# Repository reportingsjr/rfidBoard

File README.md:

General
=========
This repository has the source for a PCB that uses Power over Ethernet (PoE) to power an STM32F103 microcontroller. It has a 10mbit ethernet MAC/PHY and  3.3V (.6A, 2W) and 12V (.5A, 6W) supplies fed from a 5V (1.8A, 9W) power rail. This gives this board the capability to provide power and control for quite a few different peripherals. The first use of the circuit boards and software in this repository is to provide a lower cost and more versatile RFID based entry method for a local hackerspace, Hive13.

In this repository you will currently find two main sections: hardware, and software. The hardware section contains the KiCad files for the PoE (power over ethernet)/micro board and the rfid transceiver board (rfidBoad). The software section contains the software/firmware for the stm32f103 to support the wanted functionality (currently ethernet comms and rfid/access control).
RFID/NFC board with ethernet+PoE with numerous I/Os.

Hardware
=========

The hardware consists of two separate boards: rfidBoard and PoE. rfidBoard is simply an rfid transceiver and antenna. PoE has an STM32F103 microcontroller which is connected to a 10mbit ethernet MAC/PHY. It alsohas a power over ethernet supply that provides 5V@1.8A total. This 5 volt supply provides power for a 3.3V supply and a 12V supply. The 3.3V supply is meant for powering ICs and other electronics while the 12V supply is meant for providing power to electronic door latches (solenoids).

rfid antenna
ST Micro's antenna.exe (can be found with google) was used to calculate the antenna size for an approximately 430nH antenna. A similar antenna of different shapes can be created by using the equations in the paper "Simple Accurate Expressions for Planar Spiral Inductances" (DOI 10.1109/4.792620). The parameters I used in antenna.exe are as follows: 2 turns, 8 segments, 1mm wide conductor, 0.25mm spacing between conductors, 35um conductor thickness, and 40mm by 40mm width and length.

Software
========
There is no software or firmware set up or written yet!
It will consist of a TCP/IP stack, an RFID stack, and a user access stack.

programs needed for compilation on fedora:
sudo yum install arm-none-eabi-gcc-cs arm-none-eabi-newlib scons

To program the board an STLINK v2 programmer is needed as well as stlink (on linux).

When cloning from git cd in to software/libopencm3 and run:
`git submodule init`
`git submodule update`

To flash the board with gdb and an st-link device:
In a separate terminal run the st-link server `st-util -1`
In another terminal run `arm-none-eabi-gdb firmware.elf`
Then in gdb run `tar ext :4242`, `load`, and finally either `continue` or `run`.

Datasheets
========
The datasheets directory contains some datasheets for different chips on board.
Currently it only contains STM32 microcontroller stuff.
They are large and don't fit well in to a git repository, but it helps keep
everything together and makes things easier to investigate down the line.

Notes and Issues
=========
* TODO: Add fuses on to POE board to protect circuitry.
* Several of the components in the PoE circuitry get WAY too hot.
* C5 (4.7uF cap on the PoE input) should have the negative pin connected to  GNDA/Pout rather than VPortN.
* ~~The 12V power supply current rating pretty much maxes out what the PoE can theoretically supply. Probably should derate the 12V supply quite a lot. This means that the 3.3V, 5V, and 12V will interfere with each other which is bad.~~ Updated current rating to 500mA which provides an ok margin for total power.
* ~~D1 may need to be unidirectional. The part specified in the BOM is currently bidirectional.~~ D1 should be a schottky!
* D2 is actually a zener, not a schottky as currently shown.
* *The footprint for U1 (LTC4267) is undersized.*

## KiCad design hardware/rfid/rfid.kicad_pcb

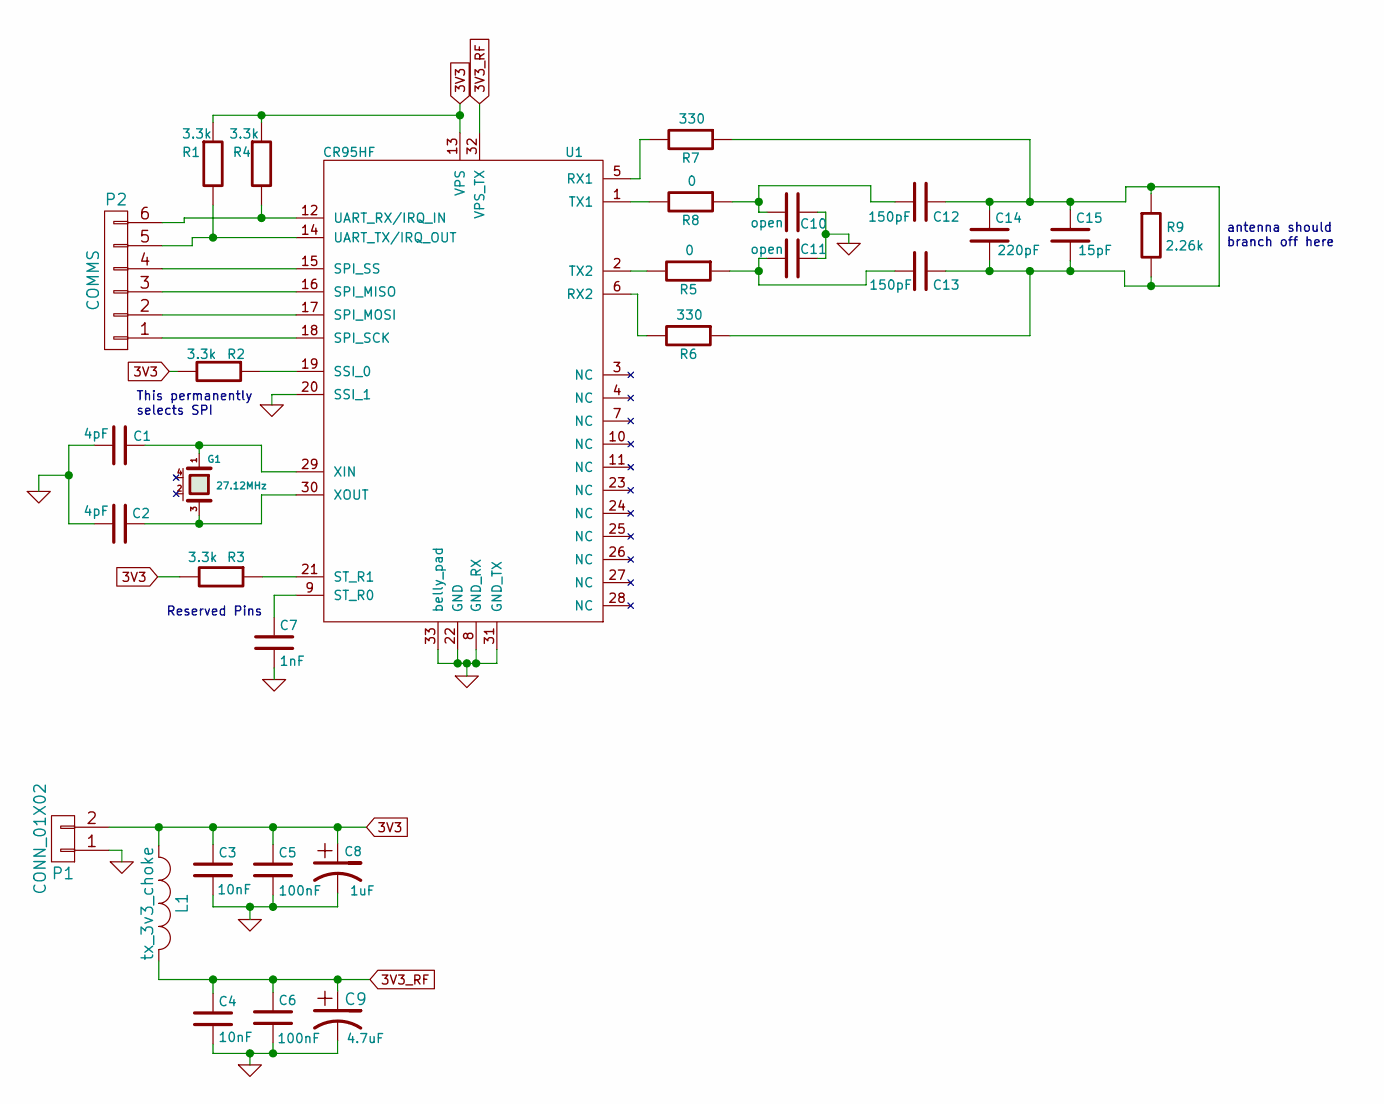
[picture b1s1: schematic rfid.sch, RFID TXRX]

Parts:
C1, C2: 4pF; SMD-0603
C3, C4: 10nF; SMD-0603
C5, C6: 100nF; SMD-0603
C7: 1nF; SMD-0603
C8: 1uF; SMD-0603
C9: 4.7uF; SMD-0805
C10, C11: open; SMD-0603
C12, C13: 150pF; SMD-0603
C14: 220pF; SMD-0603
C15: 15pF; SMD-0603
G1: 27.12MHz; 2x1.6_crystal
L1: tx_3v3_choke; SMD-0603
P1: CONN_01X02; JST_PH_2pin_side
P2: COMMS; JST_PH_6pin
R1, R2, R3, R4: 3.3k; SMD-0603
R5, R8: 0; SMD-0603
R6, R7: 330; SMD-0603
R9: 2.26k; SMD-0603
U1: CR95HF; QFN-32-1EP

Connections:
3V3: C3.1, C5.1, C8.1, L1.1, P1.2, R1.1, R2.2, R3.2, R4.1, U1.13 (VPS)
3V3_RF: C4.1, C6.1, C9.1, L1.2, U1.32 (VPS_TX)
GND: C1.2, C2.2, C3.2, C4.2, C5.2, C6.2, C7.2, C8.2, C9.2, C10.1, C11.1, P1.1, U1.8 (GND_RX), U1.20 (SSI_1), U1.22 (GND), U1.31 (GND_TX), U1.33 (belly_pad)
unnamed: C1.1, G1.1, U1.29 (XIN)
unnamed: C2.1, G1.3, U1.30 (XOUT)
unnamed: C7.1, U1.9 (ST_R0)
unnamed: C10.2, C12.2, R8.1
unnamed: C11.2, C13.2, R5.1
unnamed: C12.1, C13.1, C14.1, C14.2, C15.1, C15.2, R6.1, R7.1, R9.1, R9.2
unnamed: P2.1, U1.18 (SPI_SCK)
unnamed: P2.2, U1.17 (SPI_MOSI)
unnamed: P2.3, U1.16 (SPI_MISO)
unnamed: P2.4, U1.15 (SPI_SS)
unnamed: P2.5, R1.2, U1.14 (UART_TX/IRQ_OUT)
unnamed: P2.6, R4.2, U1.12 (UART_RX/IRQ_IN)
unnamed: R2.1, U1.19 (SSI_0)
unnamed: R3.1, U1.21 (ST_R1)
unnamed: R5.2, U1.2 (TX2)
unnamed: R6.2, U1.6 (RX2)
unnamed: R7.2, U1.5 (RX1)
unnamed: R8.2, U1.1 (TX1)

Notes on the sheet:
Reserved Pins
This permanently selects SPI
antenna should branch off here

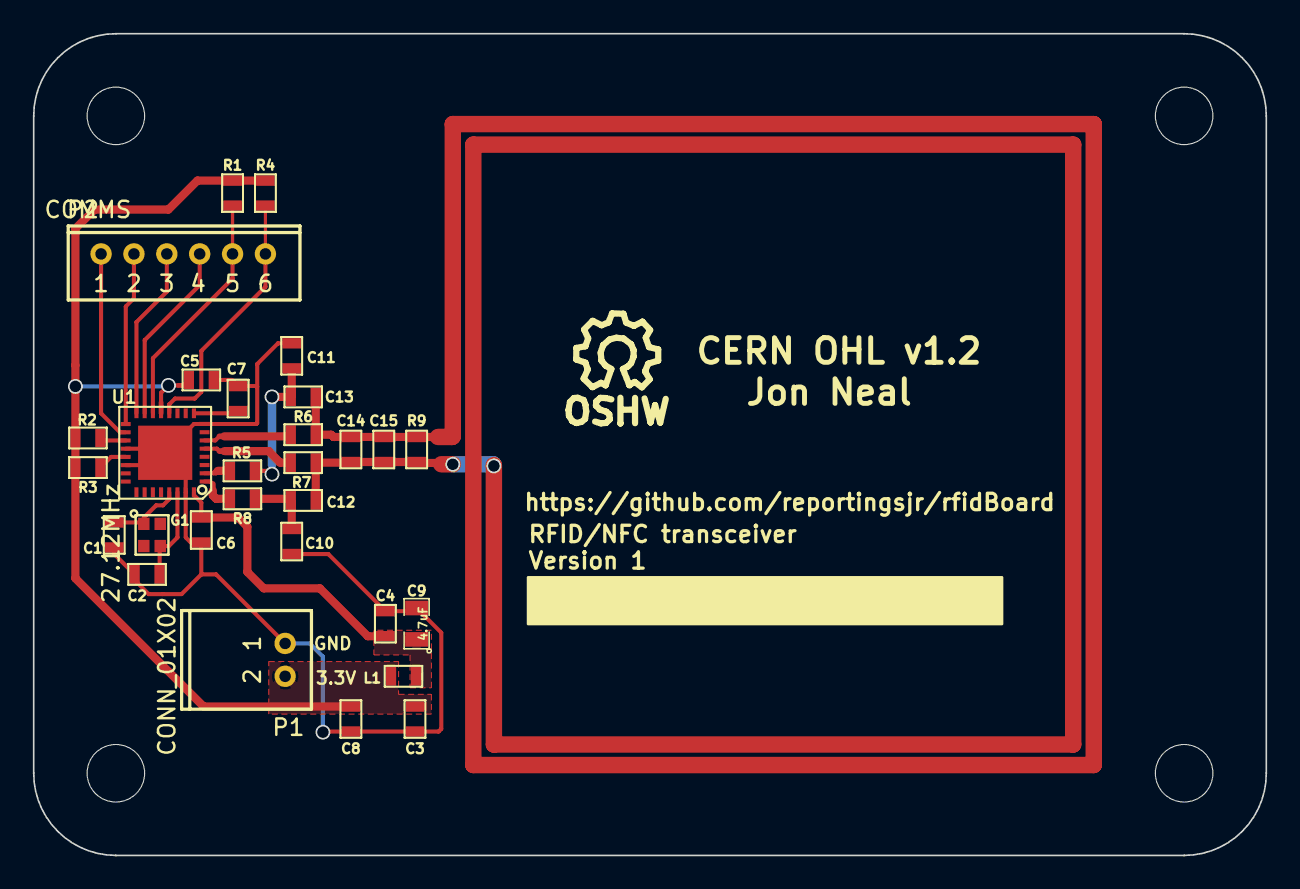
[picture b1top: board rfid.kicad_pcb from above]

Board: 2 copper layers, 75.0 x 50.0 mm, 34 parts (0 on the bottom side), 21 nets.

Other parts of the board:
MH: MountingHole_3-5mm_RevA_Date21Jun2010; MountingHole_3-5mm
MH#2, MH#3, MH#4: MountingHole_3-5mm_RevA_Date21Jun2010; MountingHole_3-5mm
SYM: Symbol_OSHW-Logo_SilkScreen_07Jul2012; Symbol_OSHW-Logo_SilkScreen

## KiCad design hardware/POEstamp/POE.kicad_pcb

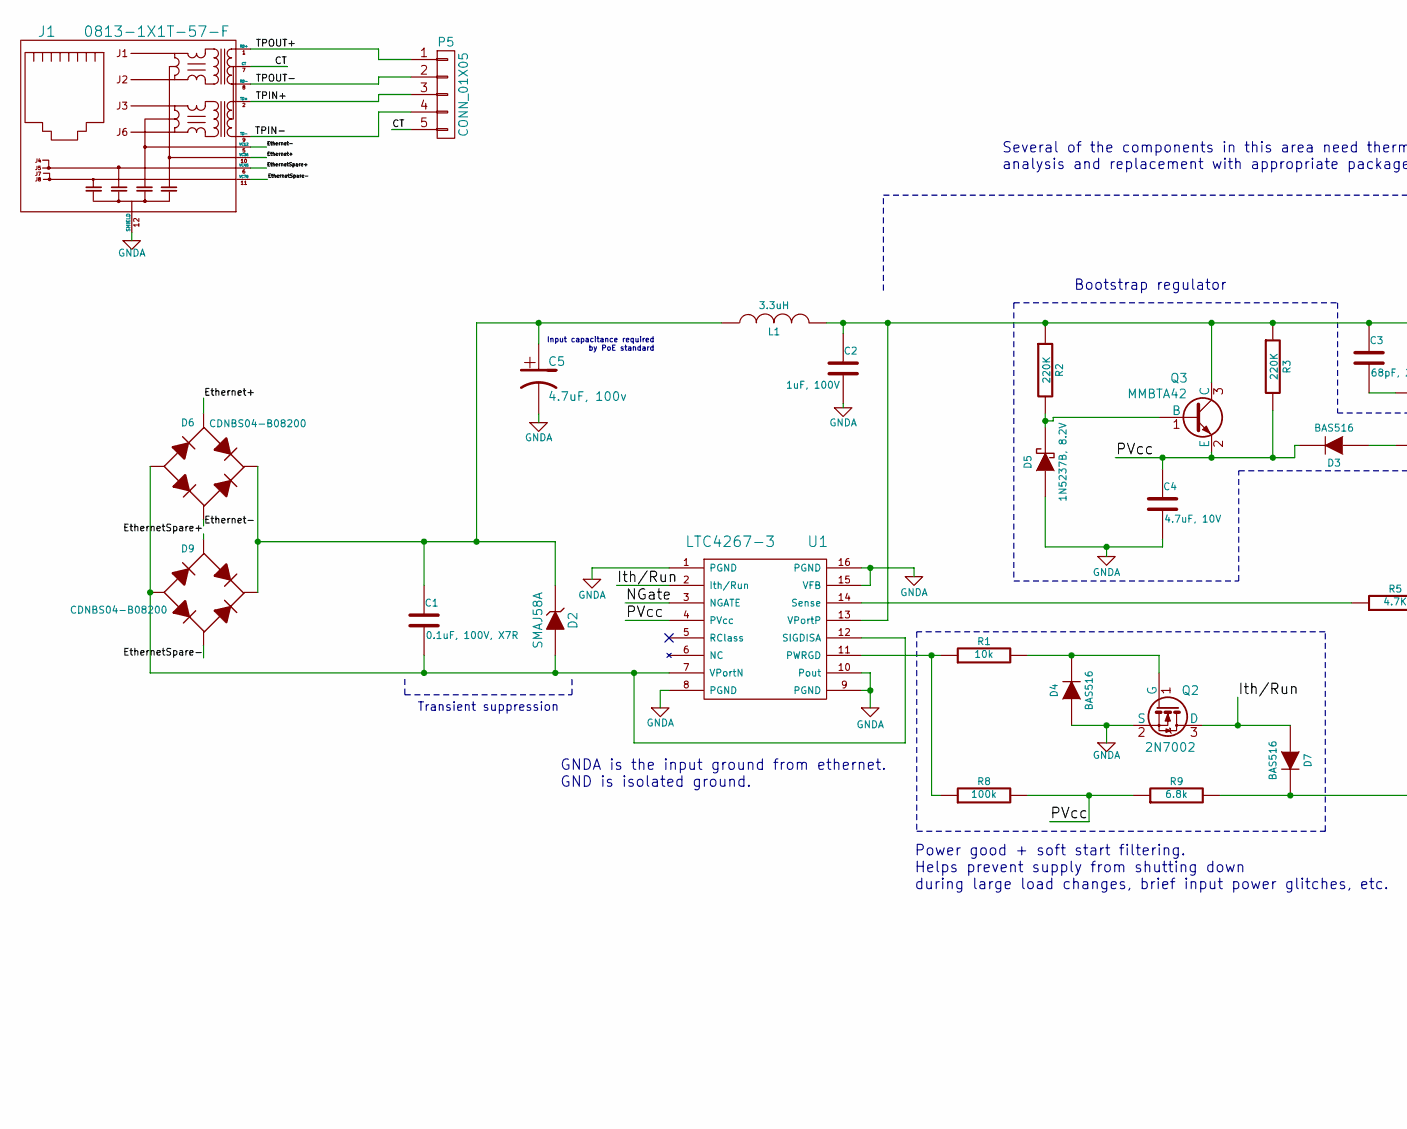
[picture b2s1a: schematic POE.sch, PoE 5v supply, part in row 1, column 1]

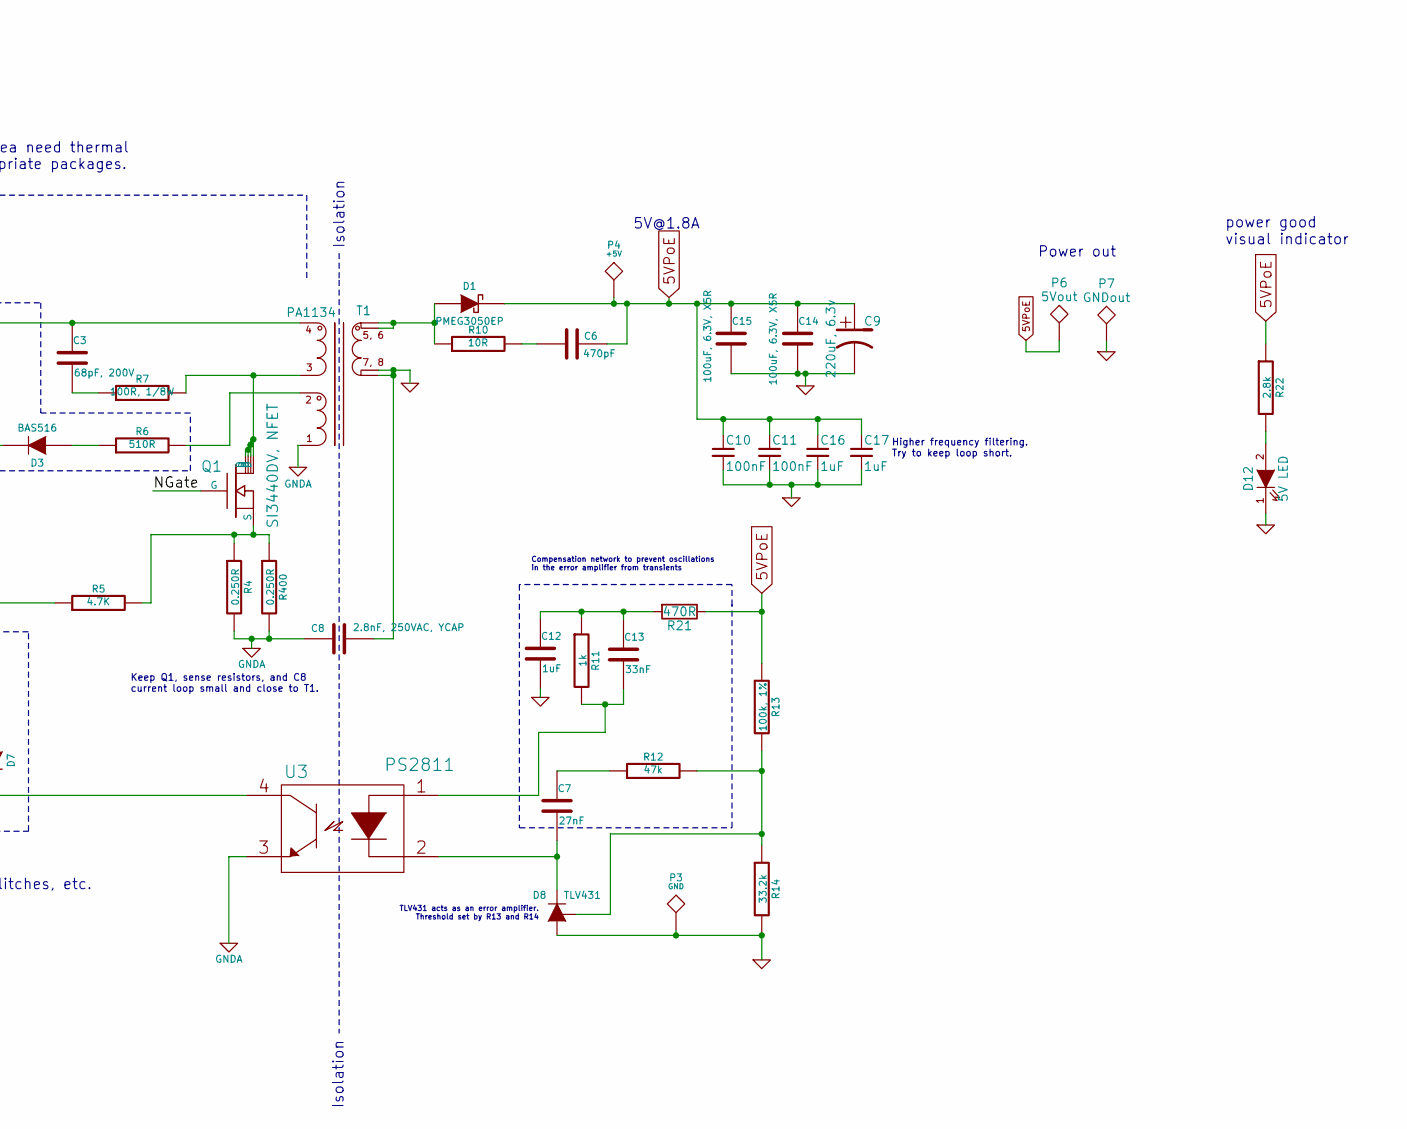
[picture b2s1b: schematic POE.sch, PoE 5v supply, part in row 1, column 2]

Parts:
C1: 0.1uF, 100V, X7R; CAPC2012X95
C2: 1uF, 100V; CAPC3216X180
C3: 68pF, 200V; CAPC1608X87
C4: 4.7uF, 10V; CAPC2012X135
C5: 4.7uF, 100v; EEE-2AA4R7UP
C6: 470pF; CAPC1608X90
C7: 27nF; CAPC2012X88
C8: 2.8nF, 250VAC, YCAP; CAPC4532X150
C9: 220uF, 6.3v; EEE-FK0J221P
C10, C11: 100nF; CAPC1608X90
C12, C16, C17: 1uF; CAPC1608X90
C13: 33nF; CAPC1608X95
C14, C15: 100uF, 6.3V, X5R; CAPC3216X180
D1: PMEG3050EP; SOD-128
D2: SMAJ58A; DIOM5436X265
D3, D4, D7: BAS516; SOD-523
D5: 1N5237B, 8.2V; SOD-123
D6, D9: CDNBS04-B08200; CDNBS04
D8: TLV431; SOT-23
D12: 5V LED; LED-0603
J1: 0813-1X1T-57-F
L1: 3.3uH; INDC2012X130
P3: GND; Measurement_Point_Round-SMD-Pad_Big
P4: +5V; Measurement_Point_Round-SMD-Pad_Big
P5: CONN_01X05; CONN-2MM-F-1x5
P6: 5Vout; 1pin
P7: GNDout; 1pin
Q1: SI3440DV, NFET; TSOP-6
Q2: 2N7002; SOT-23
Q3: MMBTA42; SOT-23
R1: 10k; RESC1608X55
R2, R3: 220K; RESC1608X55
R4, R400: 0.250R; RESC2013X65
R5: 4.7K; RESC1608X55
R6: 510R; RESC1608X55
R7: 100R, 1/8W; RESC2012X70
R8: 100k; RESC1608X55
R9: 6.8k; RESC1608X55
R10: 10R; RESC1608X55
R11: 1k; RESC1608X55
R12: 47k; RESC1608X55
R13: 100k, 1%; RESC1608X55
R14: 33.2k; RESC1608X55
R21: 470R; RESC1608X55
R22: 2.8k; RESC1608X55
T1: PA1134
U1: LTC4267-3; SOP63P600X175-16
U3: PS2811; SSOP-4

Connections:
5VPoE: C6.1, C9.1, C10.1, C11.1, C14.1, C15.1, C16.1, C17.1, D1.2 (K), P4.1, P6.1, R13.1, R21.1, R22.1
/CT: J1.7 (CT), P5.5
/Ethernet+: D6.3, J1.10 (VC36)
/Ethernet-: D6.2, J1.5 (VC12)
/EthernetSpare+: D9.3, J1.6 (VC45)
/EthernetSpare-: D9.2, J1.11 (VC78)
/Ith/Run: D7.1 (A), Q2.3 (D), U1.2 (Ith/Run)
/NGate: Q1.3 (G), U1.3 (NGATE)
/PVcc: C4.1, D3.2 (K), Q3.2 (E), R3.2, R8.2, R9.1, U1.4 (PVcc)
/TPIN+: J1.2 (TD+), P5.3
/TPIN-: J1.9 (TD-), P5.4
/TPOUT+: J1.1 (RD+), P5.1
/TPOUT-: J1.8 (RD-), P5.2
GND: C8.1, C9.2, C10.2, C11.2, C12.2, C14.2, C15.2, C16.2, C17.2, D8.3 (A), D12.1 (K), P3.1, P7.1, R14.2, T1.7, T1.8
GNDA: C2.2, C4.2, C5.2, C8.2, D4.1 (A), D5.1 (A), J1.12 (SHIELD), Q2.2 (S), R4.2, R400.2, T1.1, U1.1 (PGND), U1.8 (PGND), U1.9 (PGND), U1.10 (Pout), U1.15 (VFB), U1.16 (PGND), U3.3
unnamed: C1.1, C5.1, D2.1 (K), D6.1 (+), D9.1 (+), L1.1
unnamed: C1.2, D2.2 (A), D6.4 (-), D9.4 (-), U1.7 (VPortN), U1.12 (SIGDISA)
unnamed: C2.1, C3.1, L1.2, Q3.3 (C), R2.1, R3.1, T1.4, U1.13 (VPortP)
unnamed: C3.2, R7.1
unnamed: C6.2, R10.2
unnamed: C7.1, R12.1
unnamed: C7.2, D8.2 (K), U3.2
unnamed: C12.1, C13.1, R11.1, R21.2
unnamed: C13.2, R11.2, U3.1
unnamed: D1.1 (A), R10.1, T1.5, T1.6
unnamed: D3.1 (A), R6.1
unnamed: D4.2 (K), Q2.1 (G), R1.2
unnamed: D5.2 (K), Q3.1 (B), R2.2
unnamed: D7.2 (K), R9.2, U3.4
unnamed: D8.1 (ref), R12.2, R13.2, R14.1
unnamed: D12.2 (A), R22.2
unnamed: Q1.1 (D), Q1.2 (D), Q1.5 (D), Q1.6 (D), R7.2, T1.3
unnamed: Q1.4 (S), R4.1, R5.2, R400.1
unnamed: R1.1, R8.1, U1.11 (PWRGD)
unnamed: R5.1, U1.14 (Sense)
unnamed: R6.2, T1.2

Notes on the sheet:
GNDA is the input ground from ethernet. GND is isolated ground.
5V@1.8A
power good visual indicator
Keep Q1, sense resistors, and C8 current loop small and close to T1.
Power good + soft start filtering. Helps prevent supply from shutting down during large load changes, brief input power glitches, etc.
Isolation
Transient suppression
Input capacitance required by PoE standard
TLV431 acts as an error amplifier. Threshold set by R13 and R14
Compensation network to prevent oscillations in the error amplifier from transients
Bootstrap regulator
Higher frequency filtering. Try to keep loop short.
Power out
Several of the components in this area need thermal analysis and replacement with appropriate packages.

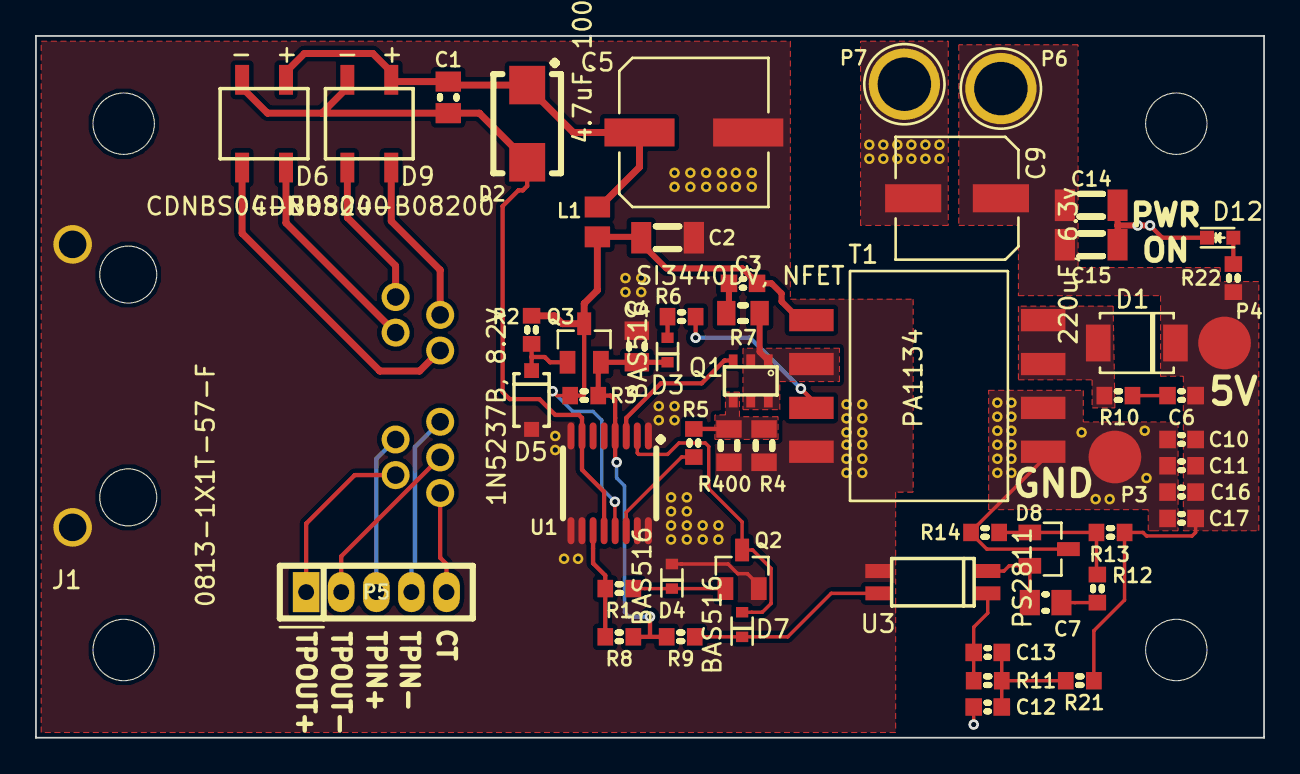
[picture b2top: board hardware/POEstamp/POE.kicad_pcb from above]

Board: 2 copper layers, 70.0 x 40.0 mm, 57 parts (1 on the bottom side), 36 nets.

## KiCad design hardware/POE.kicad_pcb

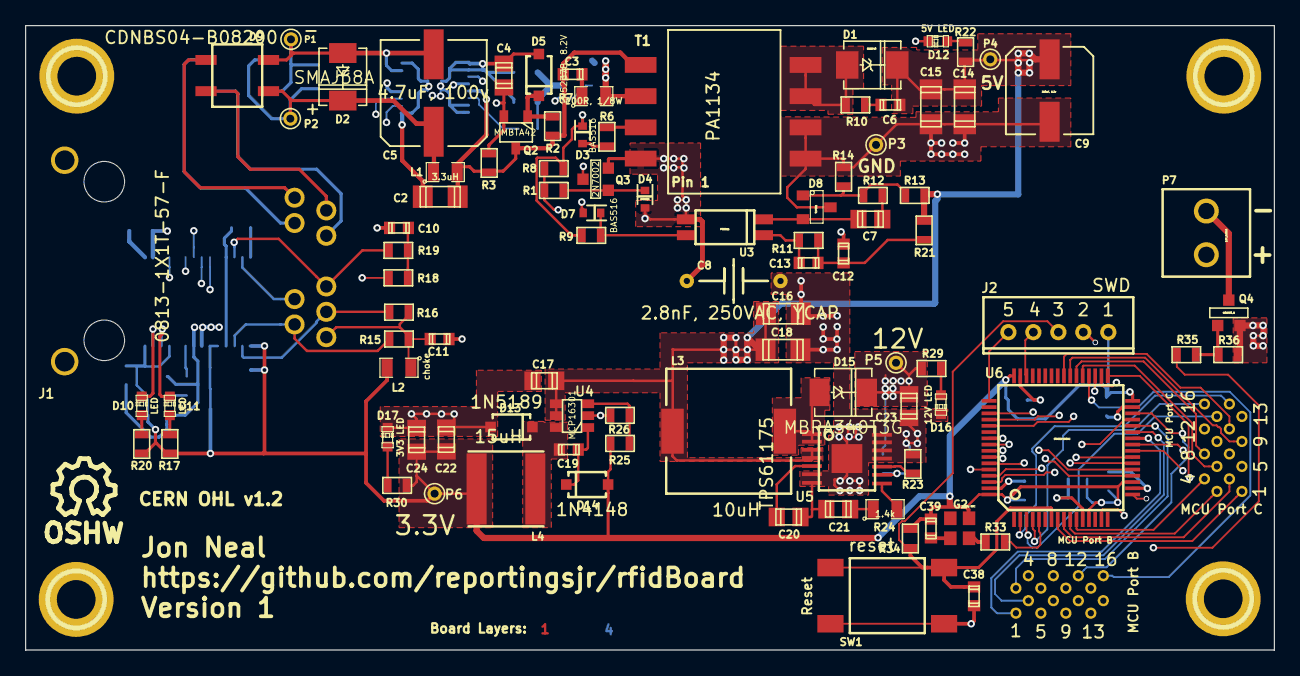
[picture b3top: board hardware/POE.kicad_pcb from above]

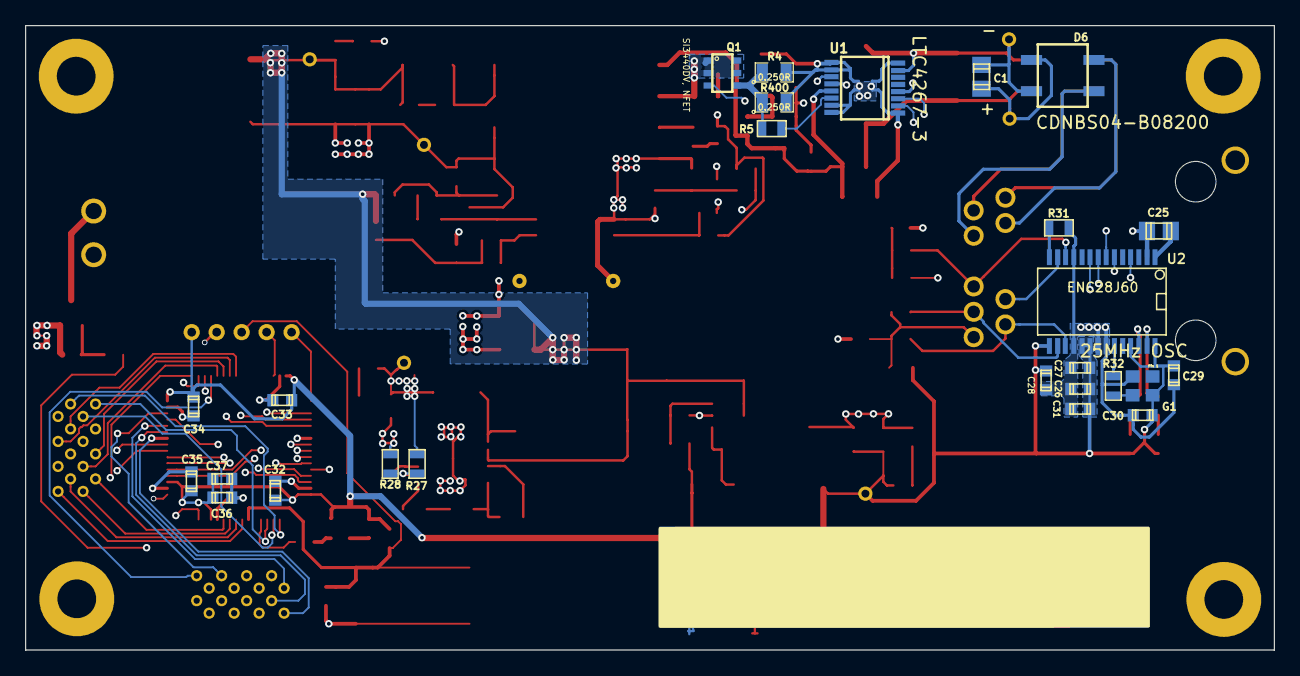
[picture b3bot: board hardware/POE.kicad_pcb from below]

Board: 4 copper layers, 100.0 x 50.0 mm, 127 parts (26 on the bottom side), 104 nets.

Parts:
1PIN, 1PIN#2, 1PIN#3, 1PIN#4: P***; 1pin
C1: 0.1uF, 100V, X7R; c_0805
C2: 1uF, 100V; c_1206
C3: 68pF, 200V; c_0603
C4: 4.7uF, 10V; c_0805
C5: 4.7uF, 100v; EEE-2AA4R7UP
C6: 470pF; c_0603
C7: 27nF; c_0805
C8: 2.8nF, 250VAC, YCAP; kemet_C900
C9: 220uF, 6.3v; EEE-FK0J221P
C10, C11: 10nF; c_0603
C12, C31, C37: 1uF; c_0603
C13: 33nF; c_0603
C14, C15: 100uF, 6.3V, X5R; c_1206
C16, C18: 10uF; c_1206
C17, C22, C24, C25: 10uF; c_0805
C19, C26, C27, C28, C29, C30, C32, C33, C34, C35, C36, C38, C39: 100nF; c_0603
C20: 47nF; c_0805
C21: 180nF; c_0805
C23: 22uF; c_0805
D1: SMB540; DO-214-AA_SMB
D2: SMAJ58A; DO-214-AC_SMA
D3, D4, D7: BAS516; SOD-523
D5: 1N5237B, 8.2V; SOD-123
D6, D9: CDNBS04-B08200; CDNBS04
D8: TLV431; SOT-23
D10, D11: LED; LED-0603
D12: 5V LED; LED-0603
D13: 1N5189; SOD-123
D14: 1N4148; SOD-123
D15: MBRA340T3G; DO-214-AC_SMA
D16: 12V LED; LED-0603
D17: 3V3 LED; LED-0603
G1: 25MHz OSC; Si501_2.5x2
G2: 24MHz OSC; Si501_2.5x2
J1: 0813-1X1T-57-F
J2: SWD; JST_PH_5pin
J3: MCU Port B; 16_pin_breakout
J4: MCU Port C; 16_pin_breakout
L1: 3.3uH; SMD-0805
L2: choke; SMD-0805
L3: 10uH; SRU1048
L4: 15uH; NR6028
P1: PoE-; PINTST
P2: PoE+; PINTST
P3: GND; PINTST
P4: +5V; PINTST
P5: +12V; PINTST
P6: +3V3; PINTST
P7: 12V_Switch; SIL2-3.5mm
Q1: SI3440DV, NFET; TSOP-6
Q2: MMBTA42; SOT-23_Inv2
Q3: 2N7002; SOT-23-GDS
Q4: MOSFET_N; SOT-23-GDS
R1, R26, R29, R36: 10k; SMD-0603
R2, R3: 220K; SMD-0603
R4, R400: 0.250R; SMD-0805
R5: 4.7K; SMD-0603
R6: 510R; SMD-0603
R7: 100R, 1/8W; SMD-0805
R8: 100k; SMD-0603
R9: 6.8k; SMD-0603
R10: 10R; SMD-0603
R11, R17, R20: 1k; SMD-0603
R12: 47k; SMD-0603
R13: 100k, 1%; SMD-0603
R14: 33.2k; SMD-0603
R15, R16, R18, R19: 49R9; SMD-0603
R21, R35: 470R; SMD-0603
R22, R30: 2.8k; SMD-0603
R23: 226k; SMD-0603
R24: 1.4k; SMD-0805
R25: 31.2k; SMD-0603
R27: 143k; SMD-0603
R28: 16.2k; SMD-0603
R31: 2.32k; SMD-0603
R32, R33: 24.9; SMD-0603
R34: 4.7k; SMD-0603
SW1: reset; TE-Switch-FSM-JSM
SYM: Symbol_OSHW-Logo_SilkScreen_07Jul2012; Symbol_OSHW-Logo_SilkScreen
T1: PA1134
U1: LTC4267-3; SSOP-16
U2: ENC28J60; SSOP-28
U3: PS2811; SSOP-4
U4: MCP16301; SOT-23-6
U5: TPS61175; HTSSOP-14-1EP
U6: STM32F100RC; LQFP64

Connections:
3V3: C22.1, C24.1, C26.1, C27.1, C28.1, C29.1, C30.2, C31.1, C32.1, C33.1, C34.1, C35.1, C36.1, C37.1, C39.2, D14.1, G1.4, G2.4, J2.1, L2.2, L4.2, P6.1, R17.2, R20.2, R25.1, R30.1, R34.2, U2.15, U2.19, U2.20, U2.25, U2.28, U6.13, U6.19, U6.32, U6.48, U6.64
5VPoE: C6.1, C9.1, C14.1, C15.1, C16.1, C17.1, C18.1, D1.2, L3.1, P4.1, R13.1, R21.2, R22.1, U4.4, U4.5, U5.3, U5.4
12V: C23.1, D15.2, P5.1, P7.1, R27.1, R29.1
/12VSwitch: R35.2, U6.15
/Ethernet+: D6.3, J1.10
/Ethernet-: D6.2, J1.5
/EthernetCS: U2.9, U6.20
/EthernetINT: U2.4, U6.17
/EthernetSCK: U2.8, U6.21
/EthernetSI: U2.7, U6.23
/EthernetSO: U2.6, U6.22
/EthernetSpare+: D9.3, J1.6
/EthernetSpare-: D9.2, J1.11
/PB0: J3.1, U6.26
/PB1: J3.2, U6.27
/PB2: J3.3, U6.28
/PB3: J3.4, U6.55
/PB4: J3.5, U6.56
/PB5: J3.6, U6.57
/PB6: J3.7, U6.58
/PB7: J3.8, U6.59
/PB8: J3.9, U6.61
/PB9: J3.10, U6.62
/PB10: J3.11, U6.29
/PB11: J3.12, U6.30
/PB12: J3.13, U6.33
/PB13: J3.14, U6.34
/PB14: J3.15, U6.35
/PB15: J3.16, U6.36
/PC0: J4.1, U6.8
/PC1: J4.2, U6.9
/PC2: J4.3, U6.10
/PC3: J4.4, U6.11
/PC4: J4.5, U6.24
/PC5: J4.6, U6.25
/PC6: J4.7, U6.37
/PC7: J4.8, U6.38
/PC8: J4.9, U6.39
/PC9: J4.10, U6.40
/PC10: J4.11, U6.51
/PC11: J4.12, U6.52
/PC12: J4.13, U6.53
/PC13: J4.14, U6.2
/PC14: J4.15, U6.3
/PC15: J4.16, U6.4
/PVcc: C4.2, D3.2, Q2.1, R3.2, R8.2, R9.1, U1.4
/TPIN+: J1.2, R18.2, U2.13
/TPIN-: J1.9, R19.2, U2.12
/TPOUT+: J1.1, R15.2, U2.17
/TPOUT-: J1.8, R16.2, U2.16
/nRST: C38.2, J2.3, R34.1, SW1.1, SW1.2, U6.7
GND: C8.2, C9.2, C10.2, C11.2, C12.2, C14.2, C15.2, C16.2, C17.2, C18.2, C20.2, C21.2, C22.2, C23.2, C24.2, C25.1, C26.2, C27.2, C28.2, C29.2, C30.1, C31.2, C32.2, C33.2, C34.2, C35.2, C36.2, C37.2, C38.1, D8.3, D12.2, D13.1, D16.2, D17.2, G1.2, J2.2, P3.1, Q4.S, R14.2, R23.2, R26.2, R28.2, R31.1, R36.2, SW1.3, SW1.4, T1.7, T1.8, U2.2, U2.11, U2.18, U2.21, U2.22, U4.2, U5.6, U5.7, U5.11, U5.12, U5.13, U5.14, U5.15, U6.12, U6.18, U6.31, U6.47, U6.60, U6.63
GNDA: C2.2, C4.1, C8.1, D4.1, D5.1, J1.12, Q3.S, R4.2, R400.2, T1.1, U1.1, U1.8, U1.9, U1.10, U1.15, U1.16, U3.3
unnamed: C1.1, C5.1, D2.2, D6.1, D9.1, L1.1, P2.1
unnamed: C1.2, C5.2, D2.1, D6.4, D9.4, P1.1, U1.7, U1.12
unnamed: C2.1, C3.1, L1.2, Q2.3, R2.1, R3.1, T1.4, U1.13
unnamed: C3.2, R7.1
unnamed: C6.2, R10.2
unnamed: C7.1, R12.1
unnamed: C7.2, D8.2, U3.2
unnamed: C10.1, R18.1, R19.1
unnamed: C11.1, J1.7, L2.1, R15.1, R16.1
unnamed: C12.1, C13.1, R11.1, R21.1
unnamed: C13.2, R11.2, U3.1
unnamed: C19.1, D14.2, U4.1
unnamed: C19.2, D13.2, L4.1, U4.6
unnamed: C20.1, U5.5
unnamed: C21.1, R24.1
unnamed: C25.2, U2.1
unnamed: C39.1, G2.2
unnamed: D1.1, R10.1, T1.5, T1.6
unnamed: D3.1, R6.1
unnamed: D4.2, Q3.G, R1.2
unnamed: D5.2, Q2.2, R2.2
unnamed: D7.1, Q3.D, U1.2
unnamed: D7.2, R9.2, U3.4
unnamed: D8.1, R12.2, R13.2, R14.1
unnamed: D10.1, R20.1
unnamed: D10.2, U2.27
unnamed: D11.1, R17.1
unnamed: D11.2, U2.26
unnamed: D12.1, R22.2
unnamed: D15.1, L3.2, U5.1, U5.2
unnamed: D16.1, R29.2
unnamed: D17.1, R30.2
unnamed: G1.3, R32.1
unnamed: G2.3, R33.1
unnamed: J2.4, U6.46
unnamed: J2.5, U6.49
unnamed: P7.2, Q4.D
unnamed: Q1.1, Q1.2, Q1.5, Q1.6, R7.2, T1.3
unnamed: Q1.3, U1.3
unnamed: Q1.4, R4.1, R5.2, R400.1
unnamed: Q4.G, R35.1, R36.1
unnamed: R1.1, R8.1, U1.11
unnamed: R5.1, U1.14
unnamed: R6.2, T1.2
unnamed: R23.1, U5.10
unnamed: R24.2, U5.8
unnamed: R25.2, R26.1, U4.3
unnamed: R27.2, R28.1, U5.9
unnamed: R31.2, U2.14
unnamed: R32.2, U2.23
unnamed: R33.2, U6.5

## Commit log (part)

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2013-11-17 Added CERN OHW license and added product and changes files.
2013-11-23 Initialized board files
2013-11-30 Added a few more components to the library and got about halfway done with the PoE power supply section.
2013-12-05 PoE schematic done up to the isolation point.
2013-12-05 Added a three pin voltage reference symbol.
2013-12-06 Created a new resistor, diode, bridge rectifier, and capacitor schematic symbols. Default KiCAD ones were way too big.
2013-12-06 Swapped out the bridge rectifier symbol on the schematic for one that is a normal size.
2013-12-07 Added several test points for the PoE power supply. Also added a 5V test LED and a note about the isolated ground.
2013-12-07 Changed PVcc from a global flag to just a label and removed some of it's lines to make the schematic clearer.
2013-12-27 Added MCP16301 symbol
2013-12-27 Added some text comments and a box around the 3.3V supply.
2013-12-27 Added a test point and power good LED to the 3.3V rail.
2013-12-28 Added text to 12V supply and added a note about the 12V supply current limitations. Also relabeled some of the test points.
2013-12-28 Fixed some wires that weren't actually connected.
2013-12-28 Created netlist so I can start work on laying out the power supply stuff.
2013-12-28 Apparently this file should come along with everything else... oops\!
2013-12-28 Missed commiting the project file.
2014-01-29 Added two SMD capacitor footprints.
2014-01-29 Added a few notes/flaws in the current design.
2014-06-22 Pins from ethernet connector to PHY were flipped.
2014-06-22 Connected passive to the ENC28J60. Only thing left for that is oscillator and connections to the micro.
2014-06-23 Starting working on a schematic symbol for the STM32F100RC.
2014-06-24 Fleshed out STM32F100RC schematic symbol. Some pins need more description added to them, but the whole component is there.
2014-06-24 Added a small .gitignore for this project. Extra KiCAD files were annoying me.
2014-06-25 Added another bypass cap to the ENC28J60 power rail. Connected power rail of STM32F100RC/micro. Also added and connected programming connector and reset button to the micro.
2014-06-26 Added bypass caps to the micro.
2014-06-27 Started schematic symbol for the RFID/NFC chip (CR95HF). Also added a note to check other symbols for belly pads. Almost forgot to do that!
2014-06-29 Updated CR95HF schematic symbol some more.
2014-07-07 Updated .gitignore to only include actual temporary kicad files. rfidAndPOE-cache.lib added as it is meant to make copying to other computers easier.
2014-07-07 Created new netlist to start associating footprints.
2014-07-15 Added two connectors to break out ports B and C on the microcontroller just in case.
2014-07-15 Removed reminder to check for solder pads on ICs. Checked everything and all are correct.
2014-07-15 Apparently missed the annotation of the two microcontroller port connectors.
2014-07-15 Added custom footprint library to preferences and updated old assignments to new name for it (rfid).
2014-07-22 Updated fp-lib-table to point to new rfid.pretty library and added Y cap component assignment.
2014-07-22 Added a revised SOD-523 footprint that has a cathode band on the silkscreen and the pins numbers are swapped to match KiCAD symbol conventions (1 for anode, 2 for cathode).
2014-07-22 Created SOD-123 footprint.
2014-07-22 Added footprint for CDNBS04 bridge rectifier.
2014-07-22 Changed TLV431 schematic symbol pin numbers to match SOT23 standard pin numbers.
2014-07-22 Assocaited LED footprints.
2014-07-22 Created 2.5mmx2mm footprint for Si501 oscillators and associated it to the two oscillators on the board.
2014-07-22 Added 5 pin JST PH connector and a 16 pin breakout footprint (16 small through holes placed close to each other).
2014-07-22 Added footprints for 3.3v and 12v power supply inductors.
2014-08-08 Added connector and transistor for external, switchable 12v output. Also reassigned some SMD package footprints that were renamed.
2014-08-09 Added missing wire junction in 12v transistor switch. Also updated some more footprints that had changed names (all are now updated).
2014-08-09 Created LDQFP64 footprint.
2014-08-09 Assigned new footprints to symbols.
2014-08-09 Updated solder mask clearance/min size.
2014-08-10 Created new symbol for Si3440 transistor as well as TSOP-6 footprint. Assigned footprint to part.
2014-08-10 TSOP-6 footprint.
2014-08-10 Added footprint for 2 pin terminal block and assigned it to a connector.
2014-08-10 Updated footprints assignments and netlist just in case.
2014-08-10 There was an extra pad way off the screen. Oops.
2014-08-10 Refreshed component file to make sure bad footprint was updated.
2014-08-10 Added kicad pcb backup file to git ignore list.
2014-08-11 Bumped up to 4 layers and changed the design rules.
2014-08-13 Moved the flyback transformer in to place as well as the switching transistor and supporting circuitry for that. Routed traces to them. Just the power good/feedback circuit left to place and route on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
2014-08-14 Organized parts in to general sections (rest of PoE stuff, microcontroller, ethernet phy, 5v supply, and 3.3v supply are the groupings).
2014-08-25 Placed and routed most of the enc28j60 components. Moved TPS61175 (12v boost supply) and components in to good orientation. Almost ready to route. Added ground plane on most of the board.
2014-08-25 Positions the 3.3v supply.
2014-08-25 Routed 3.3V supply.
2014-08-25 Finished routing microcontroller breakouts and peripherals.
2014-08-26 Added OSHW logo (should really be OHW), url for github repo, my name, and number identifiers for each board layer.
2014-08-26 Moved hardware stuff in to its own folder.
2014-08-26 Put license (CERN OHL v1.2) text on silkscreen.
2014-08-26 Moved around a buch more reference designators. Also changed one trace.
2014-08-26 Created gerbers to send to fab.
2014-08-30 Moved around another few silkscreens and generated new gerbers.
2014-09-14 Renamed rfidAndPOE stuff to just POE since rfid board will be separate.
2014-09-14 Started rfid board project file and added cr95hf symbol to schematic to start.
2014-09-17 Finished doing suggested pull ups, grounding, etc of certain pins. Added six pin connector for comms to micro. Not yet connected.
2014-09-18 Added power connector and power conditioning passives.
2014-09-22 Annotated schematic, generated netlist, and assigned footprints to all of the passives. Only connectors, IC, and crystal footprints have to be made and assigned.
2014-09-22 Created footprints from crystal and two JST connectors (6 pin vertical TH and 2 pin side entry TH).
2014-09-22 Imported netlist and parts in to pcb.
2014-09-24 Updated info about board issues.
2014-09-26 Updated readme to provide more information about the project.
2014-09-26 Moved components around on rfid board. They are kinda where they need to go now. Need to figure out what size PCB should be before anything else.
2014-09-28 Added some information about the antenna calculations to the README.
2014-09-28 Moved components to about where they should go and started routing some traces.
2014-09-29 Added flood fills for power stuff and connected antenna to RF passives.
2014-09-29 Rounded corners of PCB just because I can. added ground planes and finished routing everything. Added some information text (name, license, github link, etc).
2014-09-29 Generated gerbers for rfid board and moved POE gerbers to a new folder.
2014-09-29 A few vias weren't connected to the ground net, fixed that. Also added a zipped up version of the gerbers that were sent to oshpark.
2014-09-29 Added note in readme to add fuses to POE stuff.
2014-10-04 Moved plus and minus sign on POE bridge rectifier test points a handful of commits ago. Didn't actually need to so I swapped them back again.
2014-10-06 Added a few datasheets and reference manuals for STM32 micros.
2014-10-13 Start of a linker script for STM32F103. This should be about the minimum required to successfully link.
2014-10-16 Wrong programming manual.
2014-10-26 Removed some fluff that was not needed.
2014-11-14 Updated readme and actually removed the code in software/ this time.
2015-01-29 Deleted libopencm3 files.
2015-01-29 Added basic chibios SPI demo.
2015-01-29 Added firmware build folders to gitignore.
2015-01-31 Initialized cr95hf driver files.
2015-02-17 Basic echo test for STM32F100 to CR95HF spi communications is working.
2015-03-11 Random stuff. Not working currently.
2015-03-13 Updates to start using chibios 3.
2015-03-19 Moved cr95h code in to separate files.
2015-03-20 Fleshing out cr95hf init function.
2015-03-20 Changed from passing structs to passing struct pointers.
2015-03-24 Removed compile time optimization as it was causing issues. Flipped around pin input/output definitions. Oops.
2015-03-24 Removed some trailing whitespace and moved some variables to file scope to act as faux defines.
2015-03-24 Renamed folder to correct mcu.
2015-03-26 Trying to debug chibios mailboxes.
2015-03-28 Cleaning up the rest of the functions to use the interrupt.
2015-03-30 Added some spiUnselects between commands sent to cr95hf. This is required by the IC.
2015-03-30 Removed unnecessary spiSelect and spiUnselect.
2015-04-02 Changed from mailbox based reading thread to an event flag based one. The mailbox will now send data to other threads with a mailbox instead of recieving data over threads.
2015-04-03 Started updating other driver functions
2015-04-05 Added basic sendrecv command and a global tx buffer.
2015-04-19 Added some interrupt debugging code.
2015-04-21 Added datasheet for the NFC/RFID IC.
2015-04-22 Updating makefile to match updates in chibios
2015-04-22 Chibios changed the way thread functions are defined. Updating to reflect this change.
2015-04-24 Added some more comments and a function to further tune the IC for topaz rfid cards.
2015-05-03 Figured out why I could not talk to NFC tags after putting the CR95HF in the idle state. Setting protocol after idle fixes this issue.
2015-05-04 Split the difference NFC commands out in to separate functions. Updated makefile to use c99 standards when compiling.
2015-05-26 Rewrote topazRID, topazRALL, and sendRecv functions to now return data.
2015-05-26 void function for every NFC forum type 2 command. Moving away from topaz since it is different from everyone else and just went out of production.
2015-05-27 Implemented basic sens_req, all_req, sdd_req, and sel_req NFC-A commands. Commented out all of the topaz commands since I am moving away from topaz.
2015-06-01 implemented basic nfc forum type 2 tag read and write
2015-06-02 Added source files for an enc28j60 driver by atx.name
2015-11-21 Reorganizing hardware folder in to separate folders for separate boards.
2015-11-21 Quite a handful of changes to the POEstamp hardware as a start: * Removed all of the extra components from copying the POE files. * Fixed a couple of incorrect components in the schematic. * Fixed th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
2015-11-21 Generated new netlist.
2015-11-21 Included BOM info on everything except transistors. Updated many footprints to IPC footprints. Also added a SOD-128 footprint.
2015-11-21 Finished adding BOM info to schematic. Swapped around a couple more symbols and footprints. Ran DRC and corrected one error.
2015-11-21 Mislabeled SOD-128 footprint pads.
2015-11-21 Added note about replacing components in the non isolated side due to thermal issues.
2015-11-22 Initial component arrangement.
2015-11-22 Added board outline and 3.5mm mounting holes on a 60mmx30mm grid.
2015-11-22 Almost everything is in an OK spot on the PCB.
2015-11-22 Added ground zones and silkscreened the isolation path.
2015-11-23 Almost all traces routed sans ground connections on the ethernet side.
2015-11-23 Added annotation silkscreen on the back as well as URl to this project, OSHW logo, etc.
2015-11-23 Arranging a few parts on silkscreen a bit differently, also adjusted min size of soldermask to be a bit smaller.
2015-11-23 reorganizing where all of the gerbers go.
2015-12-31 Minor update to the Makefile
